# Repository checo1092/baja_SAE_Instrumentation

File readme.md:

## Instrumentation of a Baja SAE vehicle.
Desing and implementation of a system monitor the estatus of a Baja SAE Vehicle.

***
## Files
1. /CAD		3D drawings.
2. /CAE		KiCad desings.
3. /code		The microcontroller files.
4. /interface		Matlab-Symulink app interface.

***

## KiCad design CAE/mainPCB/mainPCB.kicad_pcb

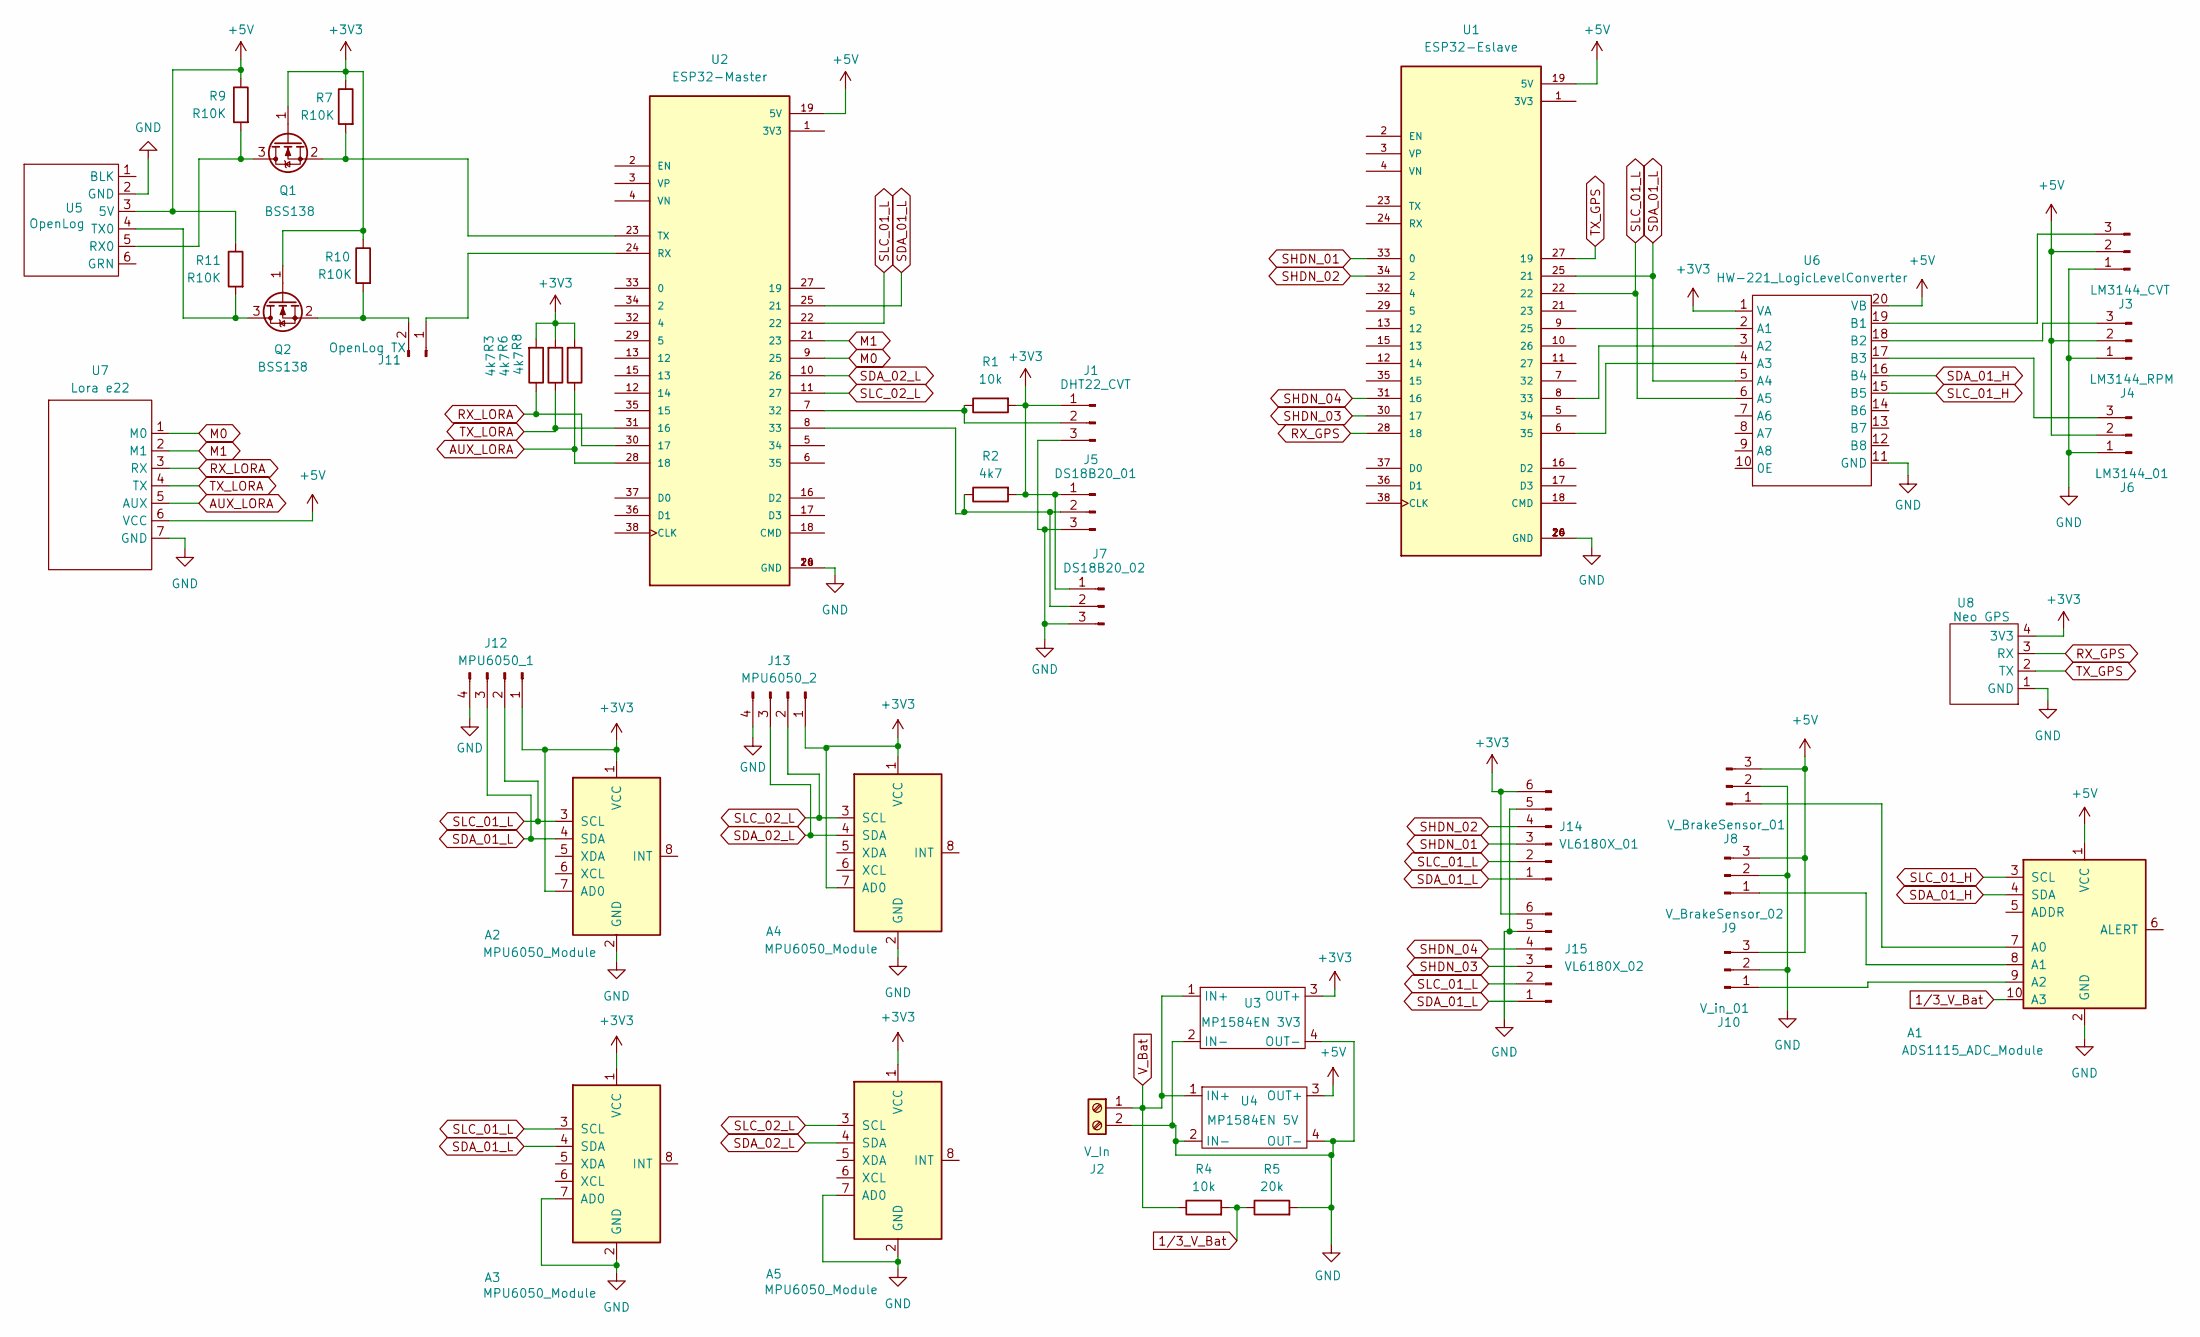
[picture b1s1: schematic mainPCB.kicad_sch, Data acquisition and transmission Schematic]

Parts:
A1: ADS1115_ADC_Module; ADC1115_ADC_Module
A2, A3, A4, A5: MPU6050_Module
J1: DHT22_CVT; PinHeader_1x03_P2.54mm_Vertical
J2: V_In; TerminalBlock_bornier-2_P5.08mm
J3: LM3144_CVT; PinHeader_1x03_P2.54mm_Vertical
J4: LM3144_RPM; PinHeader_1x03_P2.54mm_Vertical
J5: DS18B20_01; PinHeader_1x03_P2.54mm_Vertical
J6: LM3144_01; PinHeader_1x03_P2.54mm_Vertical
J7: DS18B20_02; PinHeader_1x03_P2.54mm_Vertical
J8: V_BrakeSensor_01; PinHeader_1x03_P2.54mm_Vertical
J9: V_BrakeSensor_02; PinHeader_1x03_P2.54mm_Vertical
J10: V_in_01; PinHeader_1x03_P2.54mm_Vertical
J11: OpenLog TX; PinHeader_1x02_P2.54mm_Vertical
J12: MPU6050_1; PinHeader_1x04_P2.54mm_Vertical
J13: MPU6050_2; PinHeader_1x04_P2.54mm_Vertical
J14: VL6180X_01; PinHeader_1x06_P2.54mm_Vertical
J15: VL6180X_02; PinHeader_1x06_P2.54mm_Vertical
Q1, Q2: BSS138; SOT-23
R1, R4: 10k; R_Axial_DIN0207_L6.3mm_D2.5mm_P7.62mm_Horizontal
R2, R3, R6, R8: 4k7; R_Axial_DIN0207_L6.3mm_D2.5mm_P7.62mm_Horizontal
R5: 20k; R_Axial_DIN0207_L6.3mm_D2.5mm_P7.62mm_Horizontal
R7, R9, R10, R11: R10K; R_Axial_DIN0207_L6.3mm_D2.5mm_P7.62mm_Horizontal
U1: ESP32-Eslave; ESPRESSIF_ESP32-DEVKITC-32UE; PARTREV V4
U2: ESP32-Master; ESPRESSIF_ESP32-DEVKITC-32UE; PARTREV V4
U3: MP1584EN 3V3; MP1584EN
U4: MP1584EN 5V; MP1584EN
U5: OpenLog
U6: HW-221_LogicLevelConverter; HW-221
U7: Lora e22; lora_e22
U8: Neo GPS; neo_gps

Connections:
1/3_V_Bat: A1.10 (A3), R4.2, R5.1
+3V3: A2.1 (VCC), A2.7 (AD0), A3.1 (VCC), A4.1 (VCC), A4.7 (AD0), A5.1 (VCC), J1.1, J5.1, J7.1, J12.1, J13.1, J14.6, J15.6, Q1.1 (G), Q2.1 (G), R1.2, R2.2, R3.2, R6.2, R7.1, R8.2, R10.1, U3.3 (OUT+), U6.1 (VA), U8.4 (3V3)
+5V: A1.1 (VCC), J3.2, J4.2, J6.2, J8.3, J9.3, J10.3, R9.1, R11.1, U1.19 (5V), U2.19 (5V), U4.3 (OUT+), U5.3 (5V), U6.20 (VB), U7.6 (VCC)
AUX_LORA: R8.1, U2.28 (18), U7.5 (AUX)
GND: A1.2 (GND), A2.2 (GND), A3.2 (GND), A3.7 (AD0), A4.2 (GND), A5.2 (GND), A5.7 (AD0), J1.3, J2.2, J3.1, J4.1, J5.3, J6.1, J7.3, J8.2, J9.2, J10.2, J12.4, J13.4, J14.5, J15.5, R5.2, U1.14 (GND), U1.20 (GND), U1.26 (GND), U2.14 (GND), U2.20 (GND), U2.26 (GND), U3.2 (IN-), U3.4 (OUT-), U4.2 (IN-), U4.4 (OUT-), U5.2 (GND), U6.11 (GND), U7.7 (GND), U8.1 (GND)
M0: U2.9 (25), U7.1 (M0)
M1: U2.21 (23), U7.2 (M1)
unnamed: A1.7 (A0), J8.1
unnamed: A1.8 (A1), J9.1
unnamed: A1.9 (A2), J10.1
unnamed: J1.2, R1.1, U2.7 (32)
unnamed: J3.3, U6.19 (B1)
unnamed: J4.3, U6.18 (B2)
unnamed: J5.2, J7.2, R2.1, U2.8 (33)
unnamed: J6.3, U6.17 (B3)
unnamed: J11.1, U2.24 (RX)
unnamed: J11.2, Q2.2 (S), R10.2
unnamed: Q1.3 (D), R9.2, U5.5 (RX0)
unnamed: Q1.2 (S), R7.2, U2.23 (TX)
unnamed: Q2.3 (D), R11.2, U5.4 (TX0)
unnamed: U1.9 (25), U6.2 (A1)
unnamed: U1.8 (33), U6.3 (A2)
unnamed: U1.6 (35), U6.4 (A3)
RX_GPS: U1.28 (18), U8.3 (RX)
RX_LORA: R3.1, U2.30 (17), U7.3 (RX)
SDA_01_H: A1.4 (SDA), U6.16 (B4)
SDA_01_L: A2.4 (SDA), A3.4 (SDA), J12.3, J14.1, J15.1, U1.25 (21), U2.25 (21), U6.5 (A4)
SDA_02_L: A4.4 (SDA), A5.4 (SDA), J13.3, U2.10 (26)
SHDN_01: J14.3, U1.33 (0)
SHDN_02: J14.4, U1.34 (2)
SHDN_03: J15.3, U1.30 (17)
SHDN_04: J15.4, U1.31 (16)
SLC_01_H: A1.3 (SCL), U6.15 (B5)
SLC_01_L: A2.3 (SCL), A3.3 (SCL), J12.2, J14.2, J15.2, U1.22, U2.22, U6.6 (A5)
SLC_02_L: A4.3 (SCL), A5.3 (SCL), J13.2, U2.11 (27)
TX_GPS: U1.27 (19), U8.2 (TX)
TX_LORA: R6.1, U2.31 (16), U7.4 (TX)
V_Bat: J2.1, R4.1, U3.1 (IN+), U4.1 (IN+)

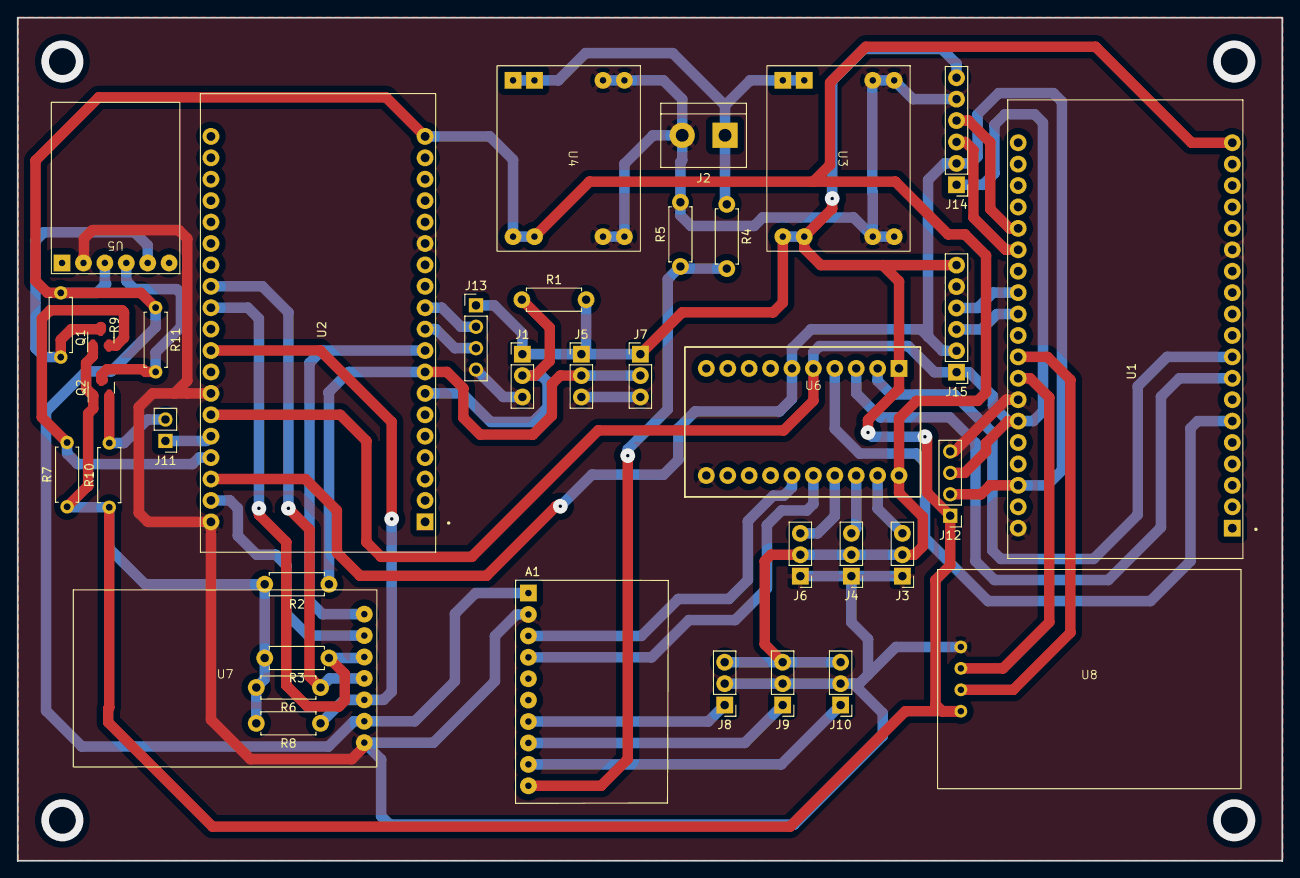
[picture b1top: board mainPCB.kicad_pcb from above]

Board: 2 copper layers, 150.0 x 100.0 mm, 37 parts (0 on the bottom side), 38 nets.

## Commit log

2023-07-11 GPS code added.
    Test code for the GPS was added
2023-07-12 Lora parameters added to the code
    Parameters to improve the LoRa comunication were added.
2023-07-13 Ring to sense the RPM added
    The designs of the ring to sense the speed of the engine were added.
2023-07-14 Budget for Unit added
    The budget for Unit electronics was added and the general budged was updated
2023-07-14 Bills folder added
    A folder with the bills was added.
2023-07-17 Height sensor designs added
    3D designs of the proposal for the suspension height sensor were added
2023-07-19 Height sensor parts updated
2023-07-19 Height sensor designs updated
2023-07-19 Interface updated
    The interface can read data from the TTGO now.
2023-07-19 Create transmission_Test.ino
    Code to test the Matlab app communication
2023-07-19 PCB design
    Designs of the main board were added
2023-07-19 Code to test the TOF sensor added
2023-07-20 Integration test of the TOF with the Matlab App
2023-07-20 Test with the TOF sensor updated
2023-07-21 Interface updated
    One function to plot the dada and another to select the serial port were added.
2023-07-21 Presentation added
    Images and files related to the presentation were added.
2023-07-21 Presentation updated
2023-07-24 Amazon receipt added
2023-07-24 Bills updated
2023-07-24 Interface updated
    The functionality to save the data into a csv file was added.
2023-07-27 SW licenses added. Engine ring updated.
    A file with the report of licenses was added. The design of the engine ring was updated.
2023-07-27 Designs of the tachometer spike added
2023-07-28 Bills added
2023-08-14 Migrated engine ring file to SolidWorks
    The design was modified to manufacture in aluminum.
2023-08-14 Rpm sensor designs added
2023-08-14 GPS codes updated
2023-08-20 Files updated
2023-08-28 CAD updated
2023-09-11 CAD designs updated
    migration from inventor to solidworks
2023-09-25 PCB updated
2023-09-26 code updated
2023-09-28 sender code updated
    MPU added
2023-10-05 PCB updated
    3D models added, rewiring for milling
2023-10-16 PCB design updated
2024-04-22 4 VL6180X distance sensor measurements
    Added:
    - Code for 4 VL6180X distance sensor measurements and more codes.
    - Organized codes in folders with more descriptive names
    - Update README
2024-07-06 Medición remota de sensores VL6180X
    - Reorganización de carpetas y nombres
    - Códigos para medición remota Arduino-MATLAB
    - Diseño de una nueva interfaz en MATLAB
2024-07-08 Documentación PBC
    Mejora en el documento word que explica la PBC
